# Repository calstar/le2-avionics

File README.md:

# LE2 Avionics 

Hardware for LE2 data acquisition (DAQ) board. 

### [Ground DAQ Spec](https://docs.google.com/document/d/13VDrlMz54n0tT20tYANPPuO85ihRtZlENfx5LBO277A/edit#)  

### [BOM](https://docs.google.com/spreadsheets/d/11PVgNdWwZuFMgkslr21FnstDzzs_OCHczlblnQA5oqc/edit#gid=0)

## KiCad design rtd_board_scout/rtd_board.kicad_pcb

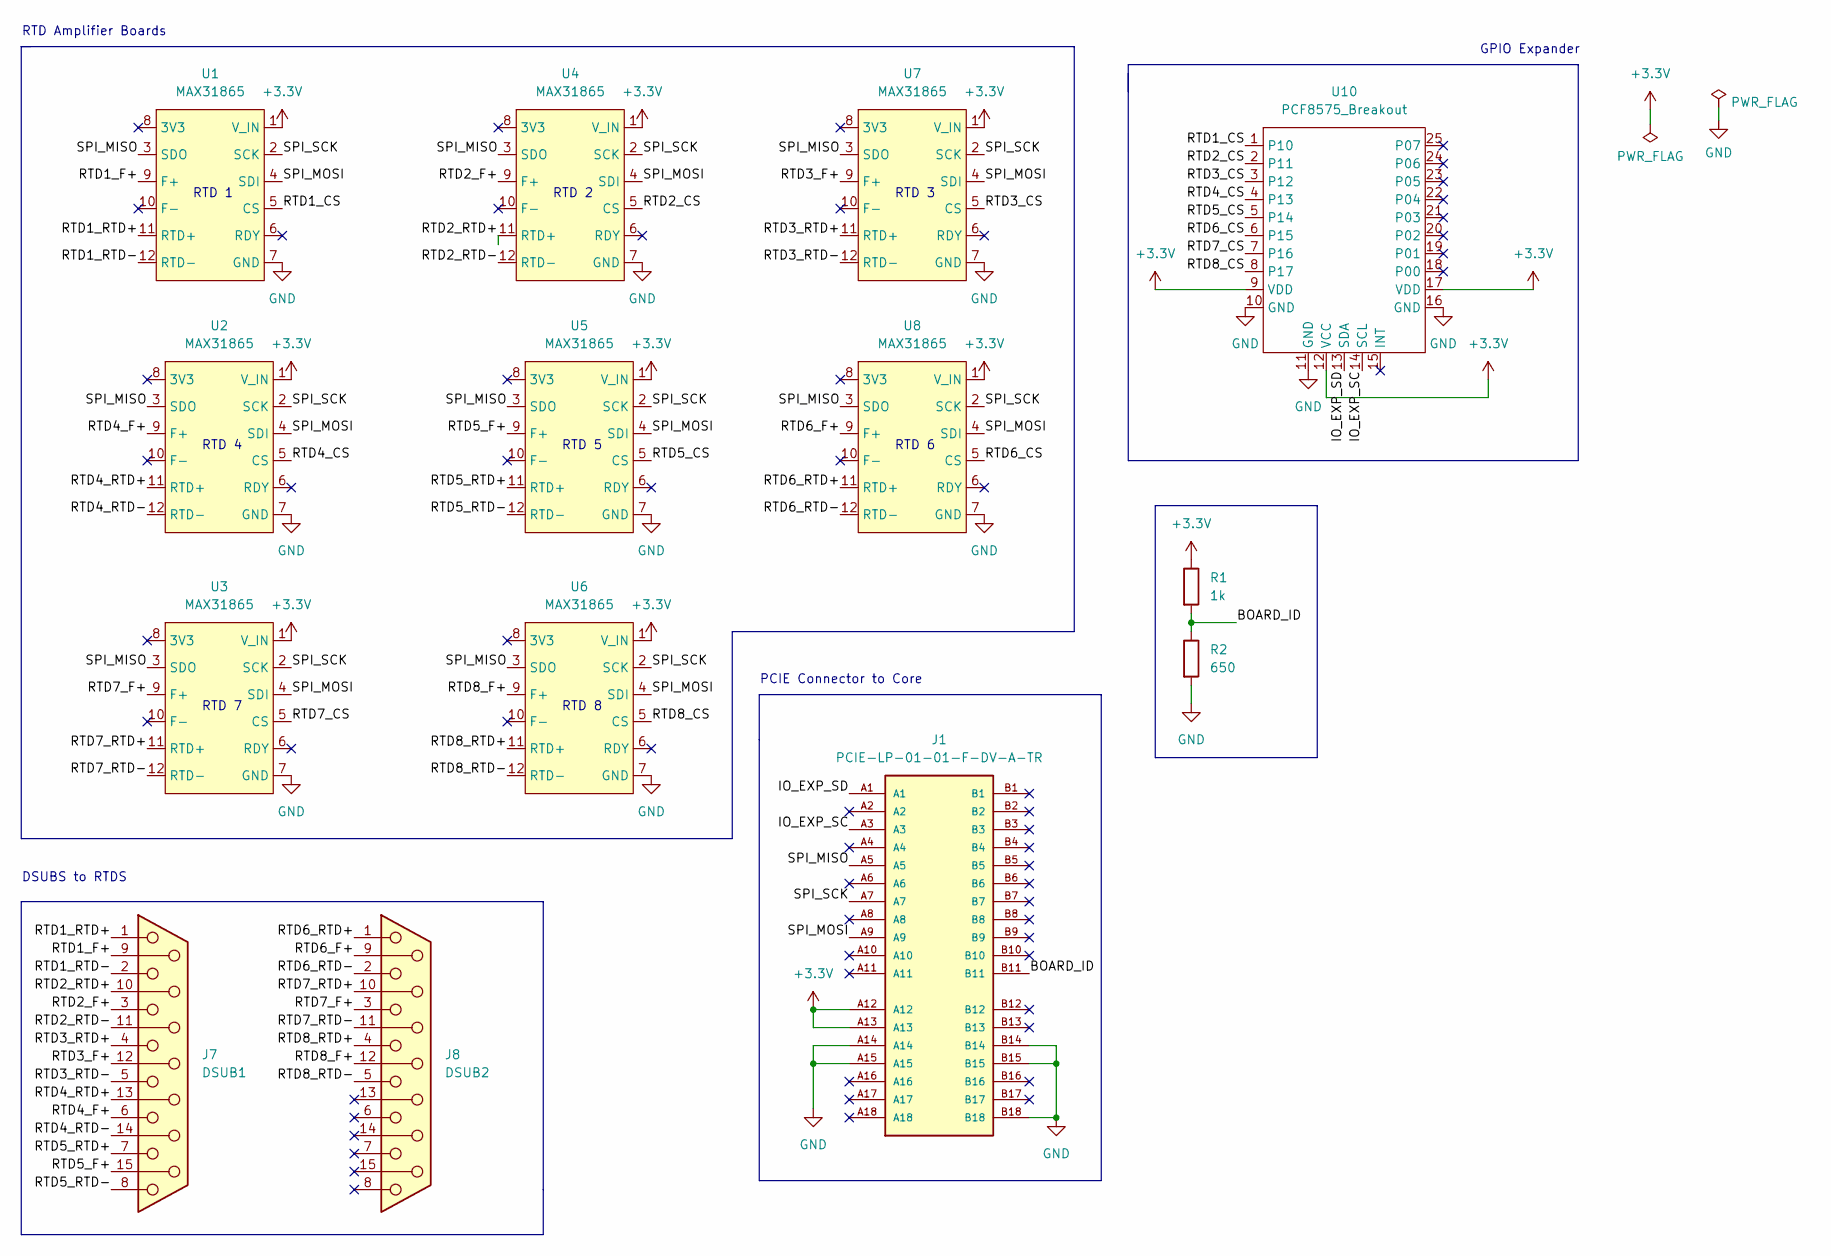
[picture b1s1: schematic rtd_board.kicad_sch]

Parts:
J1: PCIE-LP-01-01-F-DV-A-TR; BUS_PCIexpress_x1; PARTREV B
J7: DSUB1; DSUB_622-015-260-042
J8: DSUB2; DSUB_622-015-260-042
R1: 1k; R_0603_1608Metric
R2: 650; R_0603_1608Metric
U1, U2, U3, U4, U5, U6, U7, U8: MAX31865; MAX31865_Breakout
U10: PCF8575_Breakout

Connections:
+3.3V: J1.A12, J1.A13, R1.1, U1.1 (V_IN), U2.1 (V_IN), U3.1 (V_IN), U4.1 (V_IN), U5.1 (V_IN), U6.1 (V_IN), U7.1 (V_IN), U8.1 (V_IN), U10.9 (VDD), U10.12 (VCC), U10.17 (VDD)
/BOARD_ID: J1.B11, R1.2, R2.1
/IO_EXP_SC: J1.A3, U10.14 (SCL)
/IO_EXP_SD: J1.A1, U10.13 (SDA)
/RTD1_CS: U1.5 (CS), U10.1 (P10)
/RTD1_F+: J7.9, U1.9 (F+)
/RTD1_RTD+: J7.1, U1.11 (RTD+)
/RTD1_RTD-: J7.2, U1.12 (RTD-)
/RTD2_CS: U4.5 (CS), U10.2 (P11)
/RTD2_F+: J7.3, U4.9 (F+)
/RTD2_RTD+: J7.10, U4.11 (RTD+)
/RTD2_RTD-: J7.11 (P111), U4.12 (RTD-)
/RTD3_CS: U7.5 (CS), U10.3 (P12)
/RTD3_F+: J7.12, U7.9 (F+)
/RTD3_RTD+: J7.4, U7.11 (RTD+)
/RTD3_RTD-: J7.5, U7.12 (RTD-)
/RTD4_CS: U2.5 (CS), U10.4 (P13)
/RTD4_F+: J7.6, U2.9 (F+)
/RTD4_RTD+: J7.13, U2.11 (RTD+)
/RTD4_RTD-: J7.14, U2.12 (RTD-)
/RTD5_CS: U5.5 (CS), U10.5 (P14)
/RTD5_F+: J7.15, U5.9 (F+)
/RTD5_RTD+: J7.7, U5.11 (RTD+)
/RTD5_RTD-: J7.8, U5.12 (RTD-)
/RTD6_CS: U8.5 (CS), U10.6 (P15)
/RTD6_F+: J8.9, U8.9 (F+)
/RTD6_RTD+: J8.1, U8.11 (RTD+)
/RTD6_RTD-: J8.2, U8.12 (RTD-)
/RTD7_CS: U3.5 (CS), U10.7 (P16)
/RTD7_F+: J8.3, U3.9 (F+)
/RTD7_RTD+: J8.10, U3.11 (RTD+)
/RTD7_RTD-: J8.11 (P111), U3.12 (RTD-)
/RTD8_CS: U6.5 (CS), U10.8 (P17)
/RTD8_F+: J8.12, U6.9 (F+)
/RTD8_RTD+: J8.4, U6.11 (RTD+)
/RTD8_RTD-: J8.5, U6.12 (RTD-)
/SPI_MISO: J1.A5, U1.3 (SDO), U2.3 (SDO), U3.3 (SDO), U4.3 (SDO), U5.3 (SDO), U6.3 (SDO), U7.3 (SDO), U8.3 (SDO)
/SPI_MOSI: J1.A9, U1.4 (SDI), U2.4 (SDI), U3.4 (SDI), U4.4 (SDI), U5.4 (SDI), U6.4 (SDI), U7.4 (SDI), U8.4 (SDI)
/SPI_SCK: J1.A7, U1.2 (SCK), U2.2 (SCK), U3.2 (SCK), U4.2 (SCK), U5.2 (SCK), U6.2 (SCK), U7.2 (SCK), U8.2 (SCK)
GND: J1.A14, J1.A15, J1.B14, J1.B15, J1.B18, R2.2, U1.7 (GND), U2.7 (GND), U3.7 (GND), U4.7 (GND), U5.7 (GND), U6.7 (GND), U7.7 (GND), U8.7 (GND), U10.10 (GND), U10.11 (GND), U10.16 (GND)

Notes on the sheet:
DSUBS to RTDS
RTD 7
RTD 2
GPIO Expander
RTD 5
RTD 3
PCIE Connector to Core
RTD Amplifier Boards
RTD 8
RTD 4
RTD 1
RTD 6

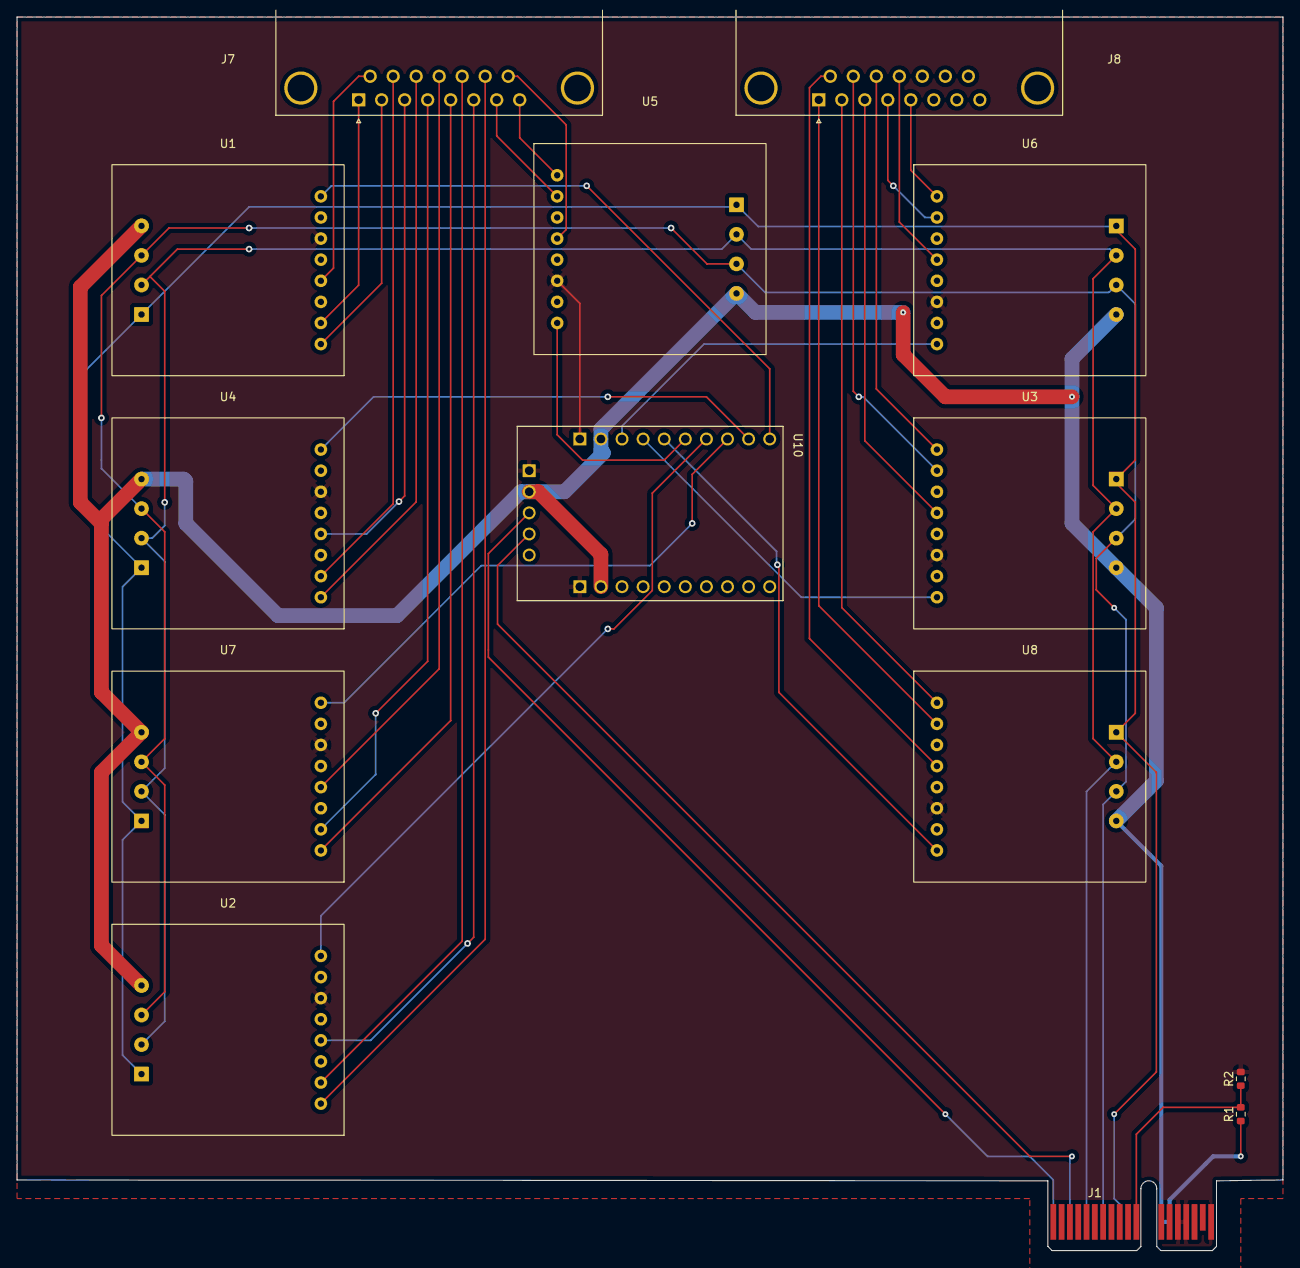
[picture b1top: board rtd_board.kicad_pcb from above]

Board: 2 copper layers, 152.4 x 148.5 mm, 14 parts (0 on the bottom side), 40 nets.

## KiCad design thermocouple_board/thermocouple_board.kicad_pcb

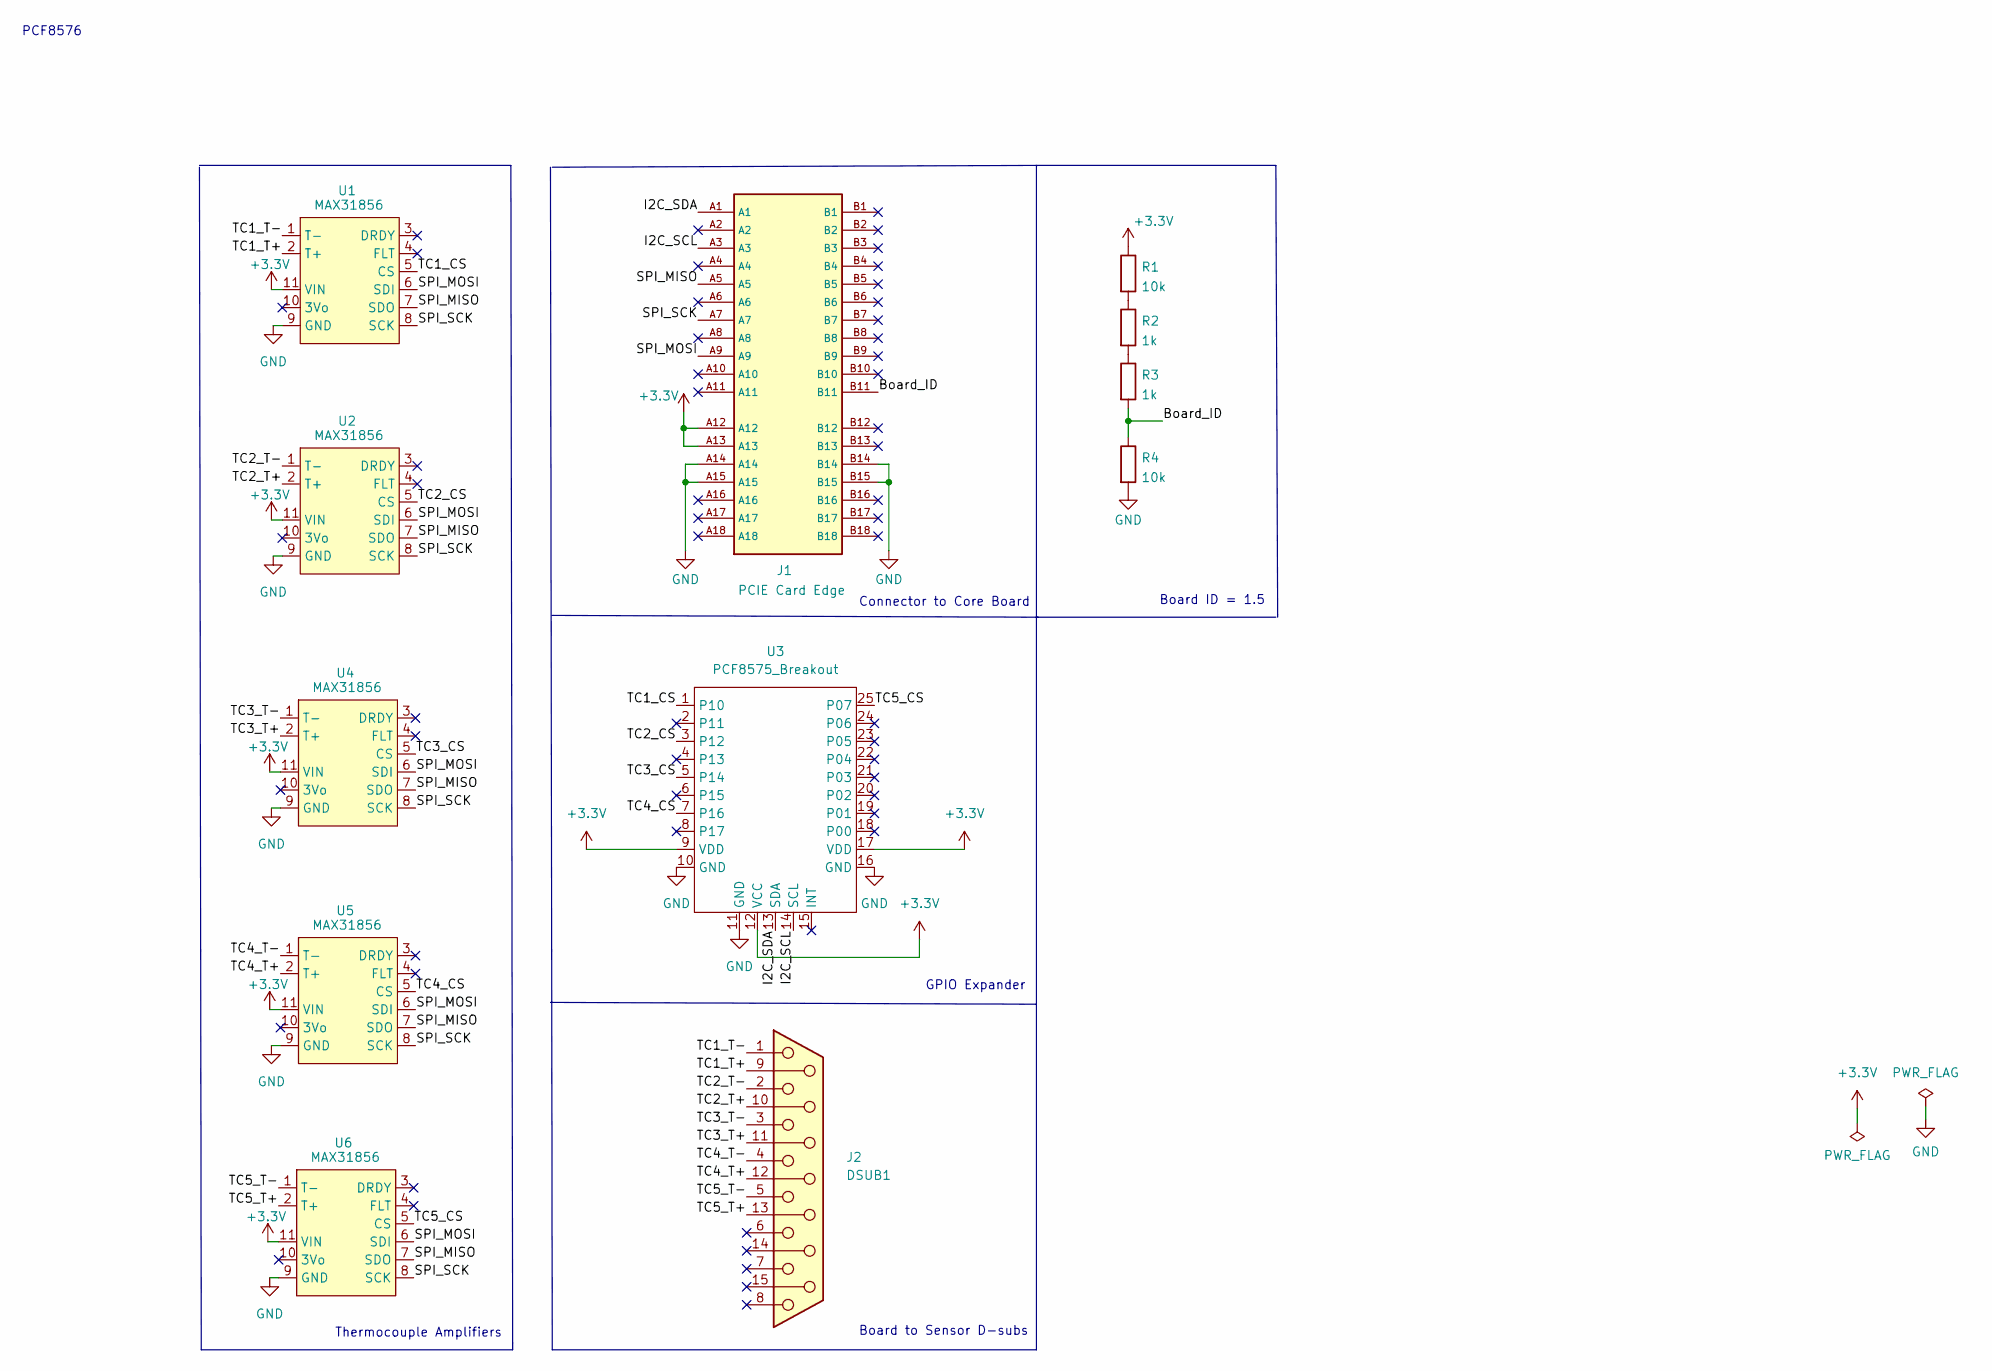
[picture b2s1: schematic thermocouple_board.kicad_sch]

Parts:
J1: PCIE Card Edge; BUS_PCIexpress_x1
J2: DSUB1; DSUB_622-015-260-042
R1, R4: 10k; R_0603_1608Metric
R2, R3: 1k; R_0603_1608Metric
U1, U2, U4, U5, U6: MAX31856; MAX31856_Breakout
U3: PCF8575_Breakout

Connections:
+3V3: J1.A12, J1.A13, R1.1, U1.11 (VIN), U2.11 (VIN), U3.9 (VDD), U3.12 (VCC), U3.17 (VDD), U4.11 (VIN), U5.11 (VIN), U6.11 (VIN)
/Board_ID: J1.B11, R3.2, R4.1
/I2C_SCL: J1.A3, U3.14 (SCL)
/I2C_SDA: J1.A1, U3.13 (SDA)
/SPI_MISO: J1.A5, U1.7 (SDO), U2.7 (SDO), U4.7 (SDO), U5.7 (SDO), U6.7 (SDO)
/SPI_MOSI: J1.A9, U1.6 (SDI), U2.6 (SDI), U4.6 (SDI), U5.6 (SDI), U6.6 (SDI)
/SPI_SCK: J1.A7, U1.8 (SCK), U2.8 (SCK), U4.8 (SCK), U5.8 (SCK), U6.8 (SCK)
/TC1_CS: U1.5 (CS), U3.1 (P10)
/TC1_T+: J2.9, U1.2 (T+)
/TC1_T-: J2.1, U1.1 (T-)
/TC2_CS: U2.5 (CS), U3.3 (P12)
/TC2_T+: J2.10, U2.2 (T+)
/TC2_T-: J2.2, U2.1 (T-)
/TC3_CS: U3.5 (P14), U4.5 (CS)
/TC3_T+: J2.11 (P111), U4.2 (T+)
/TC3_T-: J2.3, U4.1 (T-)
/TC4_CS: U3.7 (P16), U5.5 (CS)
/TC4_T+: J2.12, U5.2 (T+)
/TC4_T-: J2.4, U5.1 (T-)
/TC5_CS: U3.25 (P07), U6.5 (CS)
/TC5_T+: J2.13, U6.2 (T+)
/TC5_T-: J2.5, U6.1 (T-)
GND: J1.A14, J1.A15, J1.B14, J1.B15, R4.2, U1.9 (GND), U2.9 (GND), U3.10 (GND), U3.11 (GND), U3.16 (GND), U4.9 (GND), U5.9 (GND), U6.9 (GND)
unnamed: R1.2, R2.1
unnamed: R2.2, R3.1

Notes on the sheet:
Board to Sensor D-subs
PCF8576
Connector to Core Board
Thermocouple Amplifiers
Board ID = 1.5
GPIO Expander

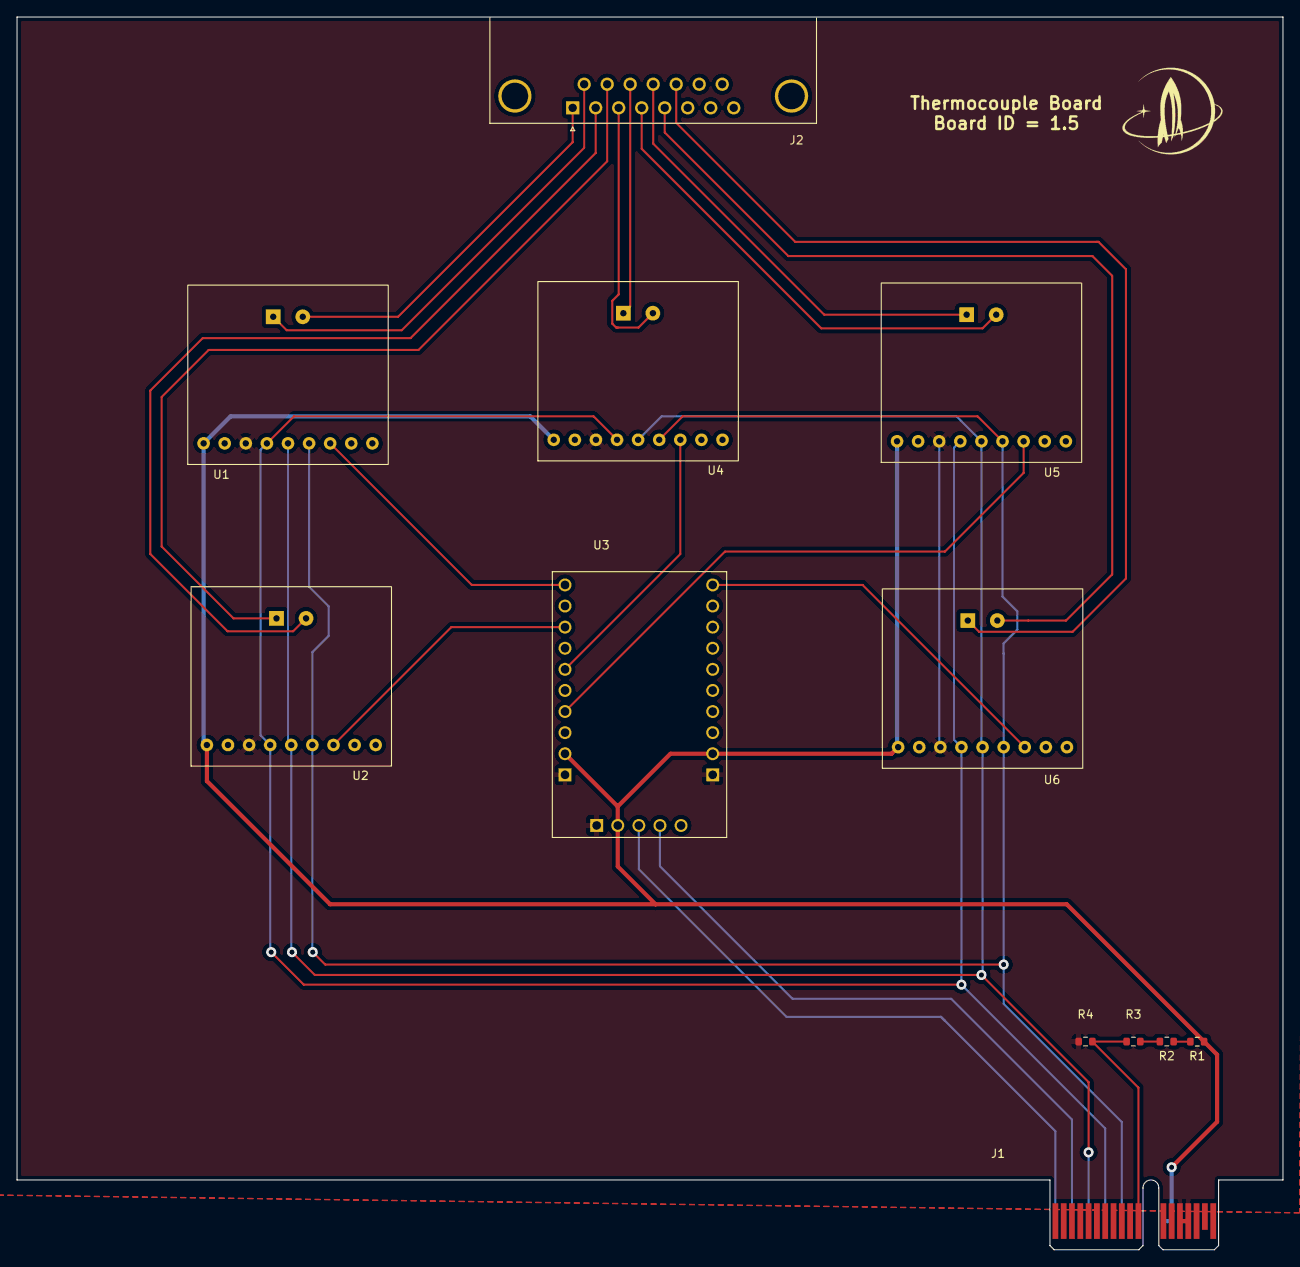
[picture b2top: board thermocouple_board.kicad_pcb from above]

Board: 2 copper layers, 152.4 x 148.4 mm, 12 parts (0 on the bottom side), 25 nets.

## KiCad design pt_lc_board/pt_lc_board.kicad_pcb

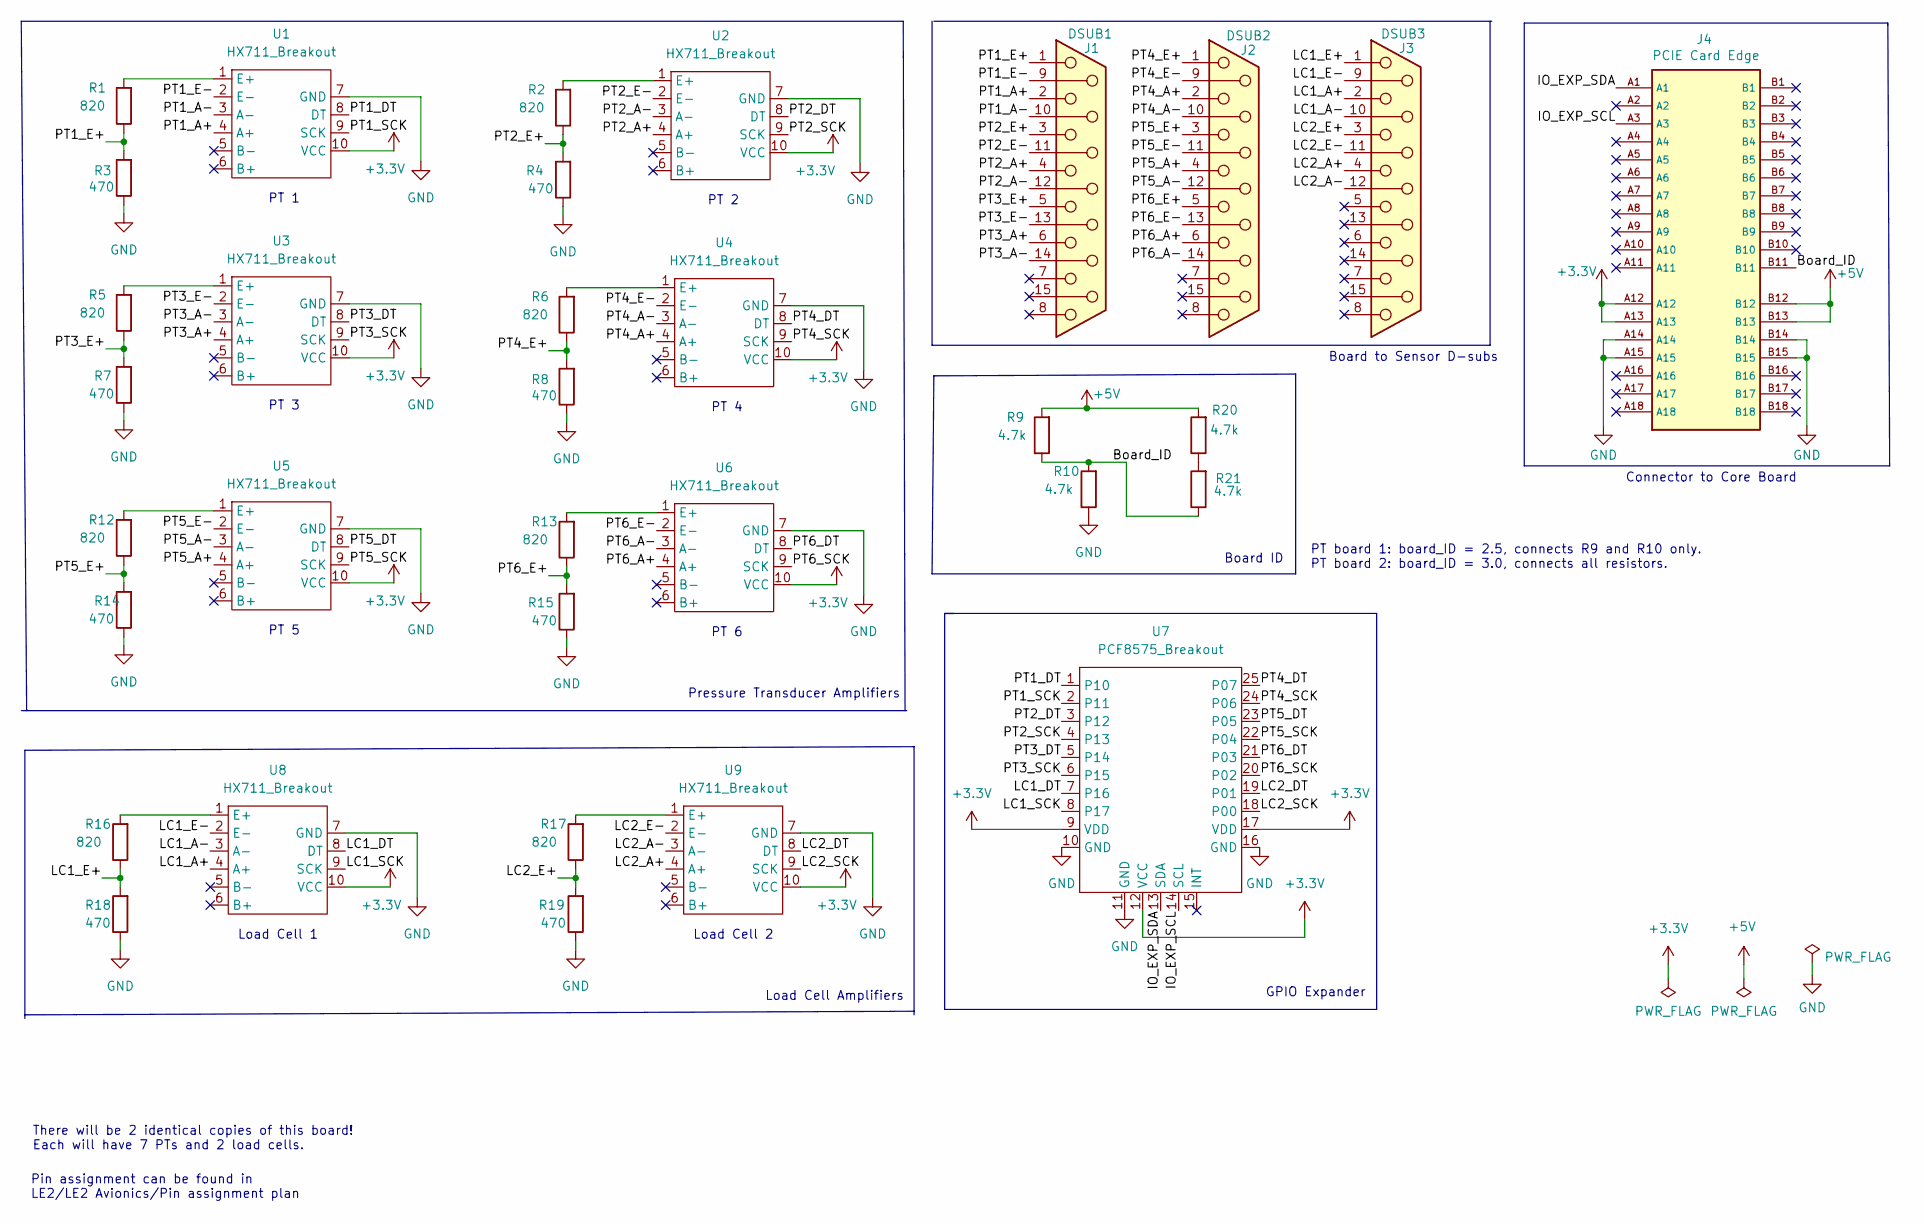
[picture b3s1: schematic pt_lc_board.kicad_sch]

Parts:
J1: DSUB1; DSUB-15_Female_Horizontal_P2.77x2.84mm_EdgePinOffset7.70mm_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
J2: DSUB2; DSUB-15_Female_Horizontal_P2.77x2.84mm_EdgePinOffset7.70mm_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
J3: DSUB3; DSUB-15_Female_Horizontal_P2.77x2.84mm_EdgePinOffset7.70mm_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
J4: PCIE Card Edge; BUS_PCIexpress_x1; PARTREV B
R1, R2, R5, R6, R12, R13, R16, R17: 820; R_0603_1608Metric
R3, R4, R7, R8, R14, R15, R18, R19: 470; R_0603_1608Metric
R9, R10, R20, R21: 4.7k; R_0603_1608Metric
U1, U2, U3, U4, U5, U6, U8, U9: HX711_Breakout; HX711_Breakout_Board
U7: PCF8575_Breakout

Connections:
+3V3: J4.A12, J4.A13, U1.10 (VCC), U2.10 (VCC), U3.10 (VCC), U4.10 (VCC), U5.10 (VCC), U6.10 (VCC), U7.9 (VDD), U7.12 (VCC), U7.17 (VDD), U8.10 (VCC), U9.10 (VCC)
+5V: J4.B12, J4.B13, R9.2, R20.2
/Board_ID: J4.B11, R9.1, R10.2, R21.1
/IO_EXP_SCL: J4.A3, U7.14 (SCL)
/IO_EXP_SDA: J4.A1, U7.13 (SDA)
/LC1_A+: J3.2, U8.4 (A+)
/LC1_A-: J3.10, U8.3 (A-)
/LC1_DT: U7.7 (P16), U8.8 (DT)
/LC1_E+: J3.1, R16.1, R18.2
/LC1_E-: J3.9, U8.2 (E-)
/LC1_SCK: U7.8 (P17), U8.9 (SCK)
/LC2_A+: J3.4, U9.4 (A+)
/LC2_A-: J3.12, U9.3 (A-)
/LC2_DT: U7.19 (P01), U9.8 (DT)
/LC2_E+: J3.3, R17.1, R19.2
/LC2_E-: J3.11 (P111), U9.2 (E-)
/LC2_SCK: U7.18 (P00), U9.9 (SCK)
/PT1_A+: J1.2, U1.4 (A+)
/PT1_A-: J1.10, U1.3 (A-)
/PT1_DT: U1.8 (DT), U7.1 (P10)
/PT1_E+: J1.1, R1.1, R3.2
/PT1_E-: J1.9, U1.2 (E-)
/PT1_SCK: U1.9 (SCK), U7.2 (P11)
/PT2_A+: J1.4, U2.4 (A+)
/PT2_A-: J1.12, U2.3 (A-)
/PT2_DT: U2.8 (DT), U7.3 (P12)
/PT2_E+: J1.3, R2.1, R4.2
/PT2_E-: J1.11 (P111), U2.2 (E-)
/PT2_SCK: U2.9 (SCK), U7.4 (P13)
/PT3_A+: J1.6, U3.4 (A+)
/PT3_A-: J1.14, U3.3 (A-)
/PT3_DT: U3.8 (DT), U7.5 (P14)
/PT3_E+: J1.5, R5.1, R7.2
/PT3_E-: J1.13, U3.2 (E-)
/PT3_SCK: U3.9 (SCK), U7.6 (P15)
/PT4_A+: J2.2, U4.4 (A+)
/PT4_A-: J2.10, U4.3 (A-)
/PT4_DT: U4.8 (DT), U7.25 (P07)
/PT4_E+: J2.1, R6.1, R8.2
/PT4_E-: J2.9, U4.2 (E-)
/PT4_SCK: U4.9 (SCK), U7.24 (P06)
/PT5_A+: J2.4, U5.4 (A+)
/PT5_A-: J2.12, U5.3 (A-)
/PT5_DT: U5.8 (DT), U7.23 (P05)
/PT5_E+: J2.3, R12.1, R14.2
/PT5_E-: J2.11 (P111), U5.2 (E-)
/PT5_SCK: U5.9 (SCK), U7.22 (P04)
/PT6_A+: J2.6, U6.4 (A+)
/PT6_A-: J2.14, U6.3 (A-)
/PT6_DT: U6.8 (DT), U7.21 (P03)
/PT6_E+: J2.5, R13.1, R15.2
/PT6_E-: J2.13, U6.2 (E-)
/PT6_SCK: U6.9 (SCK), U7.20 (P02)
GND: J4.A14, J4.A15, J4.B14, J4.B15, R3.1, R4.1, R7.1, R8.1, R10.1, R14.1, R15.1, R18.1, R19.1, U1.7 (GND), U2.7 (GND), U3.7 (GND), U4.7 (GND), U5.7 (GND), U6.7 (GND), U7.10 (GND), U7.11 (GND), U7.16 (GND), U8.7 (GND), U9.7 (GND)
unnamed: R1.2, U1.1 (E+)
unnamed: R2.2, U2.1 (E+)
unnamed: R5.2, U3.1 (E+)
unnamed: R6.2, U4.1 (E+)
unnamed: R12.2, U5.1 (E+)
unnamed: R13.2, U6.1 (E+)
unnamed: R16.2, U8.1 (E+)
unnamed: R17.2, U9.1 (E+)
unnamed: R20.1, R21.2

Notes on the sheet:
There will be 2 identical copies of this board! Each will have 7 PTs and 2 load cells.
Pressure Transducer Amplifiers
PT 4
Connector to Core Board
Board ID
Load Cell 2
Board to Sensor D-subs
PT 6
PT board 1: board_ID = 2.5, connects R9 and R10 only. PT board 2: board_ID = 3.0, connects all resistors.
PT 3
PT 2
Load Cell Amplifiers
PT 5
Pin assignment can be found in LE2/LE2 Avionics/Pin assignment plan
Load Cell 1
PT 1
GPIO Expander

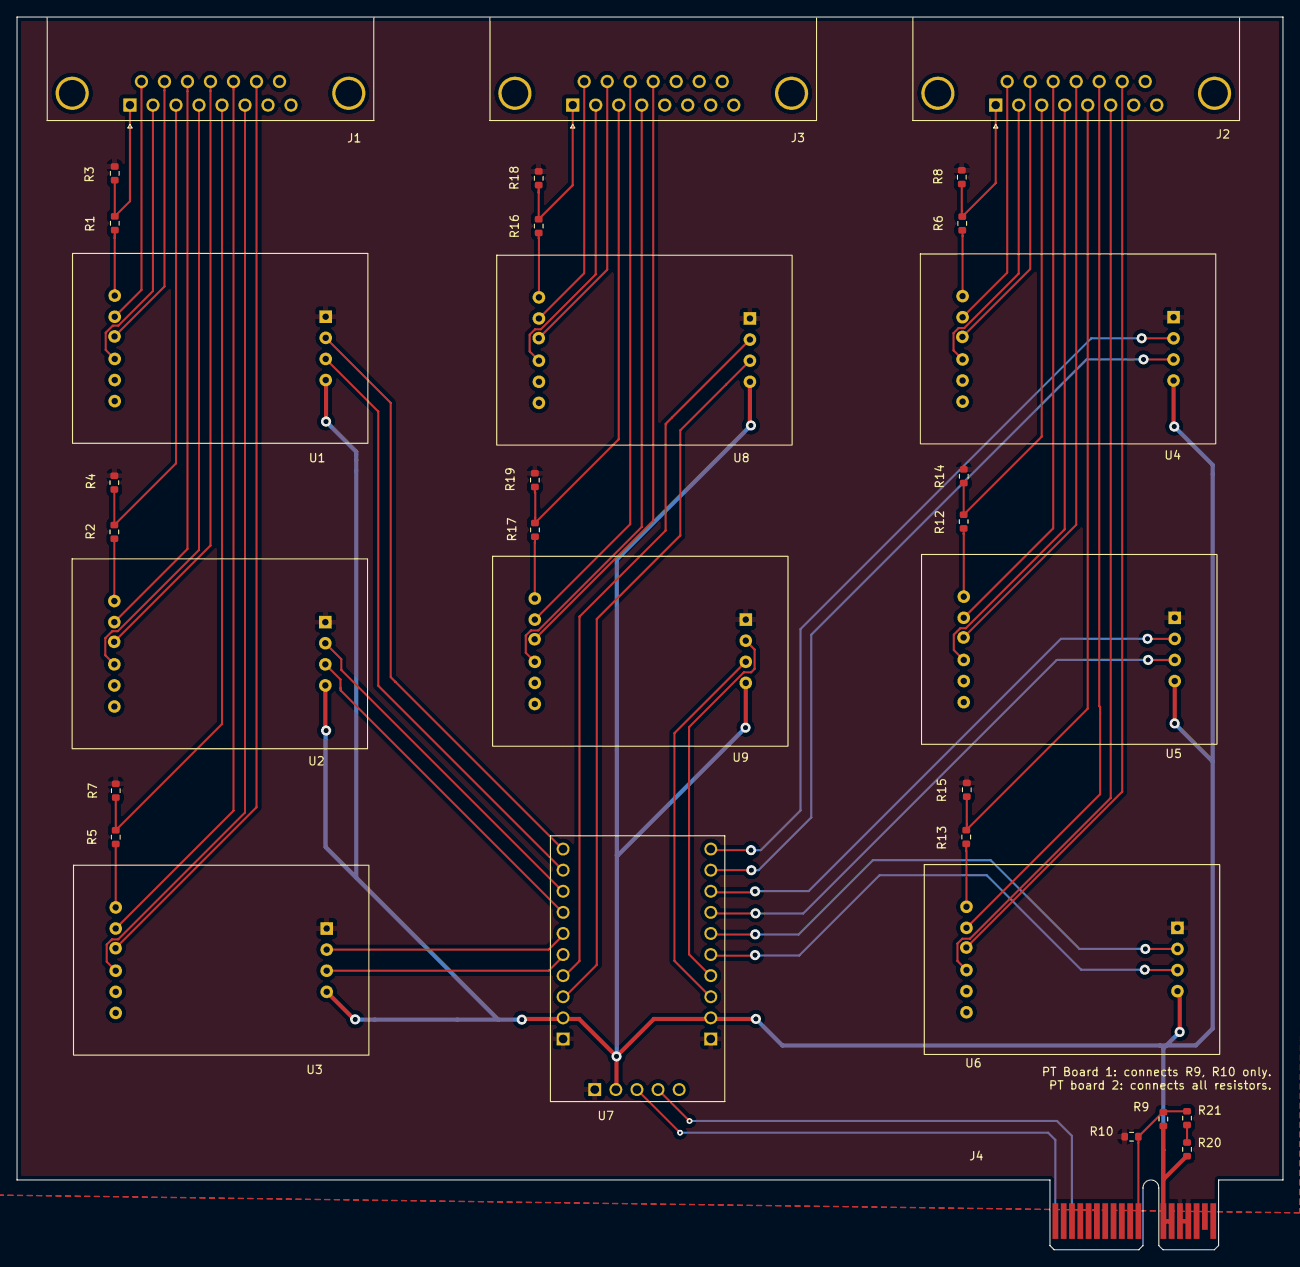
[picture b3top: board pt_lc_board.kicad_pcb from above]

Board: 2 copper layers, 152.4 x 148.4 mm, 33 parts (0 on the bottom side), 63 nets.
